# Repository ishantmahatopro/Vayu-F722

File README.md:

<h1 align="center">
  <br>
  Vayu F7
  <br>
</h1>

<h4 align="center">
A production-grade STM32F722 FPV flight controller built in KiCad, designed for
5-inch and 7-inch builds and documented the same way as a serious hardware
project should be.
</h4>

<div align="center">

</div>

<p align="center">
  <a href="#what-it-is">What it is</a> •
  <a href="#specifications">Specifications</a> •
  <a href="#hardware-overview">Hardware overview</a> •
  <a href="#pinout">Pinout</a> •
  <a href="#flight-controller-firmware">Firmware</a> •
  <a href="#building-one">Building one</a> •
  <a href="#license">License</a>
</p>

---

## What it is

*Vayu* (वायु) is the Sanskrit word for wind.

This is a 42 × 42 mm, four-layer FPV flight controller built around the
STM32F722 for 5-inch and 7-inch quads doing cinematic, telemetry, and general
performance work. It is designed to sit in the same class as well-known F722
boards while adding a cleaner power layout, a proper barometer, and a 10 V rail
sized for an HD VTX or analogue system.

The board is fully designed in KiCad.

## Specifications

| | |
|---|---|
| **MCU** | STM32F722RET6, Cortex-M7 @ 216 MHz, 512 KB flash, 256 KB RAM |
| **Gyro / accel** | ICM-42688-P on SPI1 |
| **Barometer** | BMP388 on I²C1 |
| **Blackbox** | W25Q128JVSIQ — 16 MB SPI NOR on its own bus |
| **OSD** | AT7456E analogue OSD, fitted |
| **Input** | 3S–6S (11.1–25.2 V), TVS clamp on the battery rail |
| **5 V BEC** | AP64350 synchronous buck, 5.00 V, 2 A |
| **10 V BEC** | AP64350 synchronous buck, 10.06 V, switchable for VTX rail |
| **3.3 V** | TLV62569 buck + LP5907-3.3 LDO for analogue rail |
| **Motor outputs** | 4 outputs with timer-backed DShot-capable design |
| **UARTs** | 6 total, with pads and connector-backed serial ports |
| **I²C** | 1, on the GPS connector |
| **Board** | 42 × 42 mm, 30.5 × 30.5 mm M3 mounting, 4 layers, 1.6 mm |
| **Stack-up** | F.Cu signal / **In1.Cu solid ground plane** / In2.Cu signal + ground pour / B.Cu signal |
| **Connectors** | ESC, GPS-I²C, RX, camera, VTX, USB-C |

### Power budget

| Rail | Source | Typical role |
|---|---|---|
| +10V | AP64350 buck | HD VTX / high-power video rail |
| +5V | AP64350 buck | main logic and peripheral rail |
| +3V3 | TLV62569 + LP5907 | MCU, IMU, barometer, logic |
| VBAT | input connector | raw battery feed for the switching rails |
| USB_VBUS | USB-C | debug / boot / low-power use |

## Pinout

The connector map is documented in the repo and kept together with the hardware
notes. The board includes the usual FPV stack connectors for:

| Connector | Purpose | Notes |
|---|---|---|
| ESC | Motor outputs and battery feed | 8-pin JST-SH style connector |
| GPS / I²C | GPS and barometer / compass bus | I²C and UART combination |
| HD VTX | Video and telemetry port | For HD VTX systems |
| RX | Serial receiver connection | Standard FPV receiver port |
| Camera | Camera connection | Analog / camera feed path |
| USB-C | DFU / flashing / debug | Board programming and serial access |

## Flight controller firmware

Because this project is a custom hardware layout, firmware is normally built from
upstream Betaflight or iNav sources rather than from a pre-generated target in a
factory build. The repository includes the custom target scaffold for both
firmware ecosystems so the board can be adapted to the normal upstream build
process.

### Betaflight

This repository now includes the custom Betaflight target definition at
[firmware/source/betaflight/config.h](firmware/source/betaflight/config.h).

1. Clone the upstream Betaflight repository.
2. Install the required GCC / toolchain dependencies.
3. Run `make configs` in the Betaflight tree.
4. Create a custom target directory, for example `src/config/configs/VAYUF7/`.
5. Copy [firmware/source/betaflight/config.h](firmware/source/betaflight/config.h)
   into that target directory.
6. Build the target with `make VAYUF7`.
7. Flash the resulting `.hex` via USB DFU or SWD.

The board mapping used in the target is aligned to the actual hardware:
- STM32F722RET6
- ICM-42688-P on SPI1
- BMP388 on I2C1
- AT7456E on SPI2
- W25Q128 on SPI3
- 4 motor outputs on timer-backed pins

### iNav

This repository also includes the custom iNav target files in
[firmware/source/inav/CMakeLists.txt](firmware/source/inav/CMakeLists.txt),
[firmware/source/inav/target.c](firmware/source/inav/target.c), and
[firmware/source/inav/target.h](firmware/source/inav/target.h).

1. Clone the upstream iNav repository.
2. Check out a supported stable release.
3. Create a target directory, for example `src/main/target/VAYUF7/`.
4. Copy the files from [firmware/source/inav](firmware/source/inav) into that
   target folder.
5. Configure the project with `cmake ..` inside the build directory.
6. Build the target with the normal iNav build command.
7. Flash the resulting `.hex` through USB or SWD.

> The hardware design is intentionally kept independent of any vendor-specific
> firmware stack so the board can be supported by upstream projects when the
> target is created.

## Building one

Current state — revision **R6**:

| Check | Result |
|---|---|
| KiCad DRC | **0 errors**, 0 unconnected pads (1 cosmetic silk warning) |
| KiCad ERC | **0 errors, 0 warnings** |
| Schematic ↔ board netlist | match, 483 pins / 105 nets, 0 mismatches |
| Electrical stress | all pass; worst capacitor 52.8 %, worst resistor 57.6 % of rating |
| HSE gain margin | 2.4× at C0 = 3 pF |
| Minimum via annular ring | 0.125 mm, every via ≥ 0.45 mm diameter |
| Datasheet cross-check | no mismatch found in the main design references |

The project is intentionally documented as a real engineering board, not just a
rendered concept. The repository includes a project status file, revision notes,
and hardware validation data so the design can be tracked from concept through
manufacturing readiness.

The main project constraints are documented openly:

- the board is input-limited on the battery connector at the real system level
- the 10 V rail is sized for VTX use but still obeys the regulator and layout
  limits
- all critical traces, regulator loops, and crystal areas are checked as part of
  the design review rather than left implicit

## Bill of material

The design uses practical, mainstream FPV parts that are suitable for a
production-style board and are chosen with sourcing and assembly in mind. The key
parts in the current hardware are:

| Category | Item | Notes |
|---|---|---|
| MCU | STM32F722RET6 | 32-bit F7 core, 216 MHz |
| IMU | ICM-42688-P | SPI-based gyro / accel |
| Barometer | BMP388 | I²C pressure sensor |
| Flash | W25Q128JVSIQ | 16 MB SPI NOR blackbox memory |
| OSD | AT7456E | Analog video overlay device |
| Regulators | AP64350 + LP5907 / TLV62569 | 5 V, 10 V, 3.3 V generation |
| Connectors | JST-SH / USB-C | Standard FPV and service interfaces |
| Board | 4-layer PCB | 42 × 42 mm, 30.5 × 30.5 mm mounting |

The repository is organized around the actual board design, not around a generic
marketing sheet. The hardware files, status records, and revision notes are the
source of truth for assembly and manufacturing decisions.

## BOM

The table below is the assembly BOM generated from the production files. Prices
are indicative USD unit prices from the currently displayed LCSC quantity tier
for the listed minimum order, checked on 2026-09-22. They exclude PCB
fabrication, assembly, shipping, tax, and tooling. `quote` means the public
product page did not expose a current price and should be checked in the JLCPCB
order quote.

| SL NO | LCSC NO | COMPONENT | PRICE IN USD |
|---:|---|---|---:|
| 1 | C29823 | C1, C2 - 4.7uF/50V, qty 2 | 0.0853 |
| 2 | C12891 | C10, C14, C15, C17, C8, C9 - 22uF/25V, qty 6 | 0.0904 |
| 3 | C1525 | C11, C5 - 100nF/16V, qty 2 | 0.0023 |
| 4 | C1531 | C12, C60 - 2.2nF, qty 2 | 0.0014 |
| 5 | C106203 | C13 - 22pF, qty 1 | 0.0023 |
| 6 | C3039694 | C16, C34 - 10uF/16V, qty 2 | 0.0699 |
| 7 | C307331 | C18, C21, C23, C24, C25, C26, C27, C30, C33, C35, C37, C38, C39, C40, C41, C42, C43, C46, C50, C51, C56, C58 - 100nF/50V, qty 22 | 0.0046 |
| 8 | C5199872 | C19, C20, C22, C49 - 1uF/50V, qty 4 | 0.0107 |
| 9 | C2885646 | C28, C29 - 4.7uF/16V, qty 2 | 0.0236 |
| 10 | C437557 | C3, C52, C53, C54, C55 - 4.7uF/50V, qty 5 | 0.1152 |
| 11 | C107004 | C31, C32 - 15pF, qty 2 | 0.0013 |
| 12 | C415535 | C36 - 2.2uF/16V, qty 1 | 0.0412 |
| 13 | C14663 | C4 - 100nF/50V, qty 1 | 0.0052 |
| 14 | C45783 | C47, C48 - 22uF/16V, qty 2 | 0.1037 |
| 15 | C189470 | C59 - 6.8pF, qty 1 | 0.0016 |
| 16 | C107024 | C6 - 1.8nF, qty 1 | 0.0021 |
| 17 | C107002 | C7 - 27pF, qty 1 | 0.0015 |
| 18 | C908777 | D1 - SMAJ33A, qty 1 | 0.0167 |
| 19 | C64885 | D4 - B5819W, qty 1 | 0.0091 |
| 20 | C2286 | D5 - RED 3V3, qty 1 | 0.0035 |
| 21 | C965804 | D6 - GREEN 5V, qty 1 | 0.0031 |
| 22 | C965802 | D7 - YELLOW VBAT, qty 1 | 0.0038 |
| 23 | C965807 | D8 - BLUE STATUS, qty 1 | 0.0027 |
| 24 | C1017 | FB1 - 600R@100MHz 2A, qty 1 | quote |
| 25 | C160407 | J1 - ESC 8P, qty 1 | 0.1840 |
| 26 | C53055322 | J2 - HD VTX 6P, qty 1 | 0.0349 |
| 27 | C160404 | J3 - RX 4P, qty 1 | 0.1245 |
| 28 | C53055322 | J4 - GPS/I2C 6P, qty 1 | 0.0349 |
| 29 | C160404 | J5 - CAM 4P, qty 1 | 0.1245 |
| 30 | C160404 | J6 - VTX 4P, qty 1 | 0.1245 |
| 31 | C165948 | J8 - USB-C 16P, qty 1 | 0.0971 |
| 32 | C167221 | L1 - 6.8uH FXL0630-6R8-M, qty 1 | 0.0827 |
| 33 | C189932 | L2 - 10uH SRP5030T-100M, qty 1 | 0.6640 |
| 34 | C50543 | L3 - 2.2uH SWPA4018S2R2MT, qty 1 | quote |
| 35 | C8545 | Q1 - 2N7002, qty 1 | 0.0106 |
| 36 | C20917 | Q2 - AO3400A, qty 1 | 0.0482 |
| 37 | C159047 | R1, R7 - 294k, qty 2 | 0.0004 |
| 38 | C25748 | R10 - 118k, qty 1 | 0.0013 |
| 39 | C5153958 | R11, R5 - 10.2k, qty 2 | 0.0010 |
| 40 | C2998091 | R12 - 31.6k, qty 1 | 0.0014 |
| 41 | C25744 | R13, R14, R20, R28, R34, R35, R36, R37, R38, R50 - 10k, qty 10 | 0.0017 |
| 42 | C25905 | R16, R17 - 5.1k, qty 2 | 0.0012 |
| 43 | C25879 | R18, R19, R25, R26, R39 - 2.2k, qty 5 | 0.0026 |
| 44 | C2960799 | R2, R8 - 57.6k, qty 2 | 0.0012 |
| 45 | C2909384 | R21, R22 - 75R, qty 2 | 0.0013 |
| 46 | C25804 | R23 - 10k, qty 1 | 0.0012 |
| 47 | C11702 | R24, R30, R33, R40, R41 - 1k, qty 5 | 0.0012 |
| 48 | C25741 | R27, R49 - 100k, qty 2 | 0.0013 |
| 49 | C22369194 | R29 - 100R, qty 1 | quote |
| 50 | C2909325 | R3 - 180k, qty 1 | 0.0012 |
| 51 | C25867 | R31 - 1.5k, qty 1 | 0.0013 |
| 52 | C22809 | R32 - 15k, qty 1 | 0.0014 |
| 53 | C53398 | R4 - 53.6k, qty 1 | 0.0008 |
| 54 | C2906868 | R42, R43, R44, R45, R47 - 33R, qty 5 | 0.0012 |
| 55 | C3013172 | R48 - 453k, qty 1 | 0.0013 |
| 56 | C2998160 | R6 - 25.5k, qty 1 | 0.0013 |
| 57 | C2909311 | R9 - 110k, qty 1 | 0.0009 |
| 58 | C231329 | SW1 - BOOT, qty 1 | 0.1025 |
| 59 | C2071691 | U1, U2 - AP64350SP-13, qty 2 | 1.1554 |
| 60 | C82351 | U10 - AT7456E, qty 1 | 1.7093 |
| 61 | C141836 | U3 - TLV62569DBVR, qty 1 | 0.0441 |
| 62 | C80670 | U4 - LP5907MFX-3.3, qty 1 | 0.1260 |
| 63 | C118207 | U5 - STM32F722RET6, qty 1 | 6.9322 |
| 64 | C2687116 | U6 - USBLC6-2SC6, qty 1 | 0.0221 |
| 65 | C1850418 | U7 - ICM-42688-P, qty 1 | 15.6022 |
| 66 | C779278 | U8 - BMP388, qty 1 | 3.6120 |
| 67 | C97521 | U9 - W25Q128JVSIQ, qty 1 | 1.6422 |
| 68 | C2682775 | X1 - 8MHz X32258MOB4SI 12pF, qty 1 | 0.0937 |
| 69 | C9008 | X2 - 27MHz X322527MSB4SI, qty 1 | 0.0489 |
| 70 | | PCB, qty 5 | 27.54 |
| 71 | | PCBA, qty 2 | 130

## Board renders

### - If its hard to zoom please check out /img folder to see each part of the schematic much more clearly, I tried using .pdf to .img but unfortunately u can't see the text on zooming in... hence I have taken SS of each component.

## Credits

- [KiCad](https://www.kicad.org/)
- [INAV](https://github.com/iNavFlight/inav)
- [Betaflight](https://github.com/betaflight/betaflight)
- [JLCPCB](https://jlcpcb.com/) and [LCSC](https://www.lcsc.com/)
- [Hack Club Blueprint](https://blueprint.hackclub.com/)
- The original open hardware and design process references that inspired this
  board-level documentation approach

## AI usage
This project was designed and built with the help of AI ChatGPT 5.6 precisely... AI was used to extract key important design rules for different componets pulling it off their 200pages chinglish docs ( chinese + english ). Help in creating a netlist, chosing components and drawing the schematic.
Also AI was used in writing the firmware...

> As mentioned in the resource docs, no AI was used to write slopped Journal or REAMDE.

## License

MIT

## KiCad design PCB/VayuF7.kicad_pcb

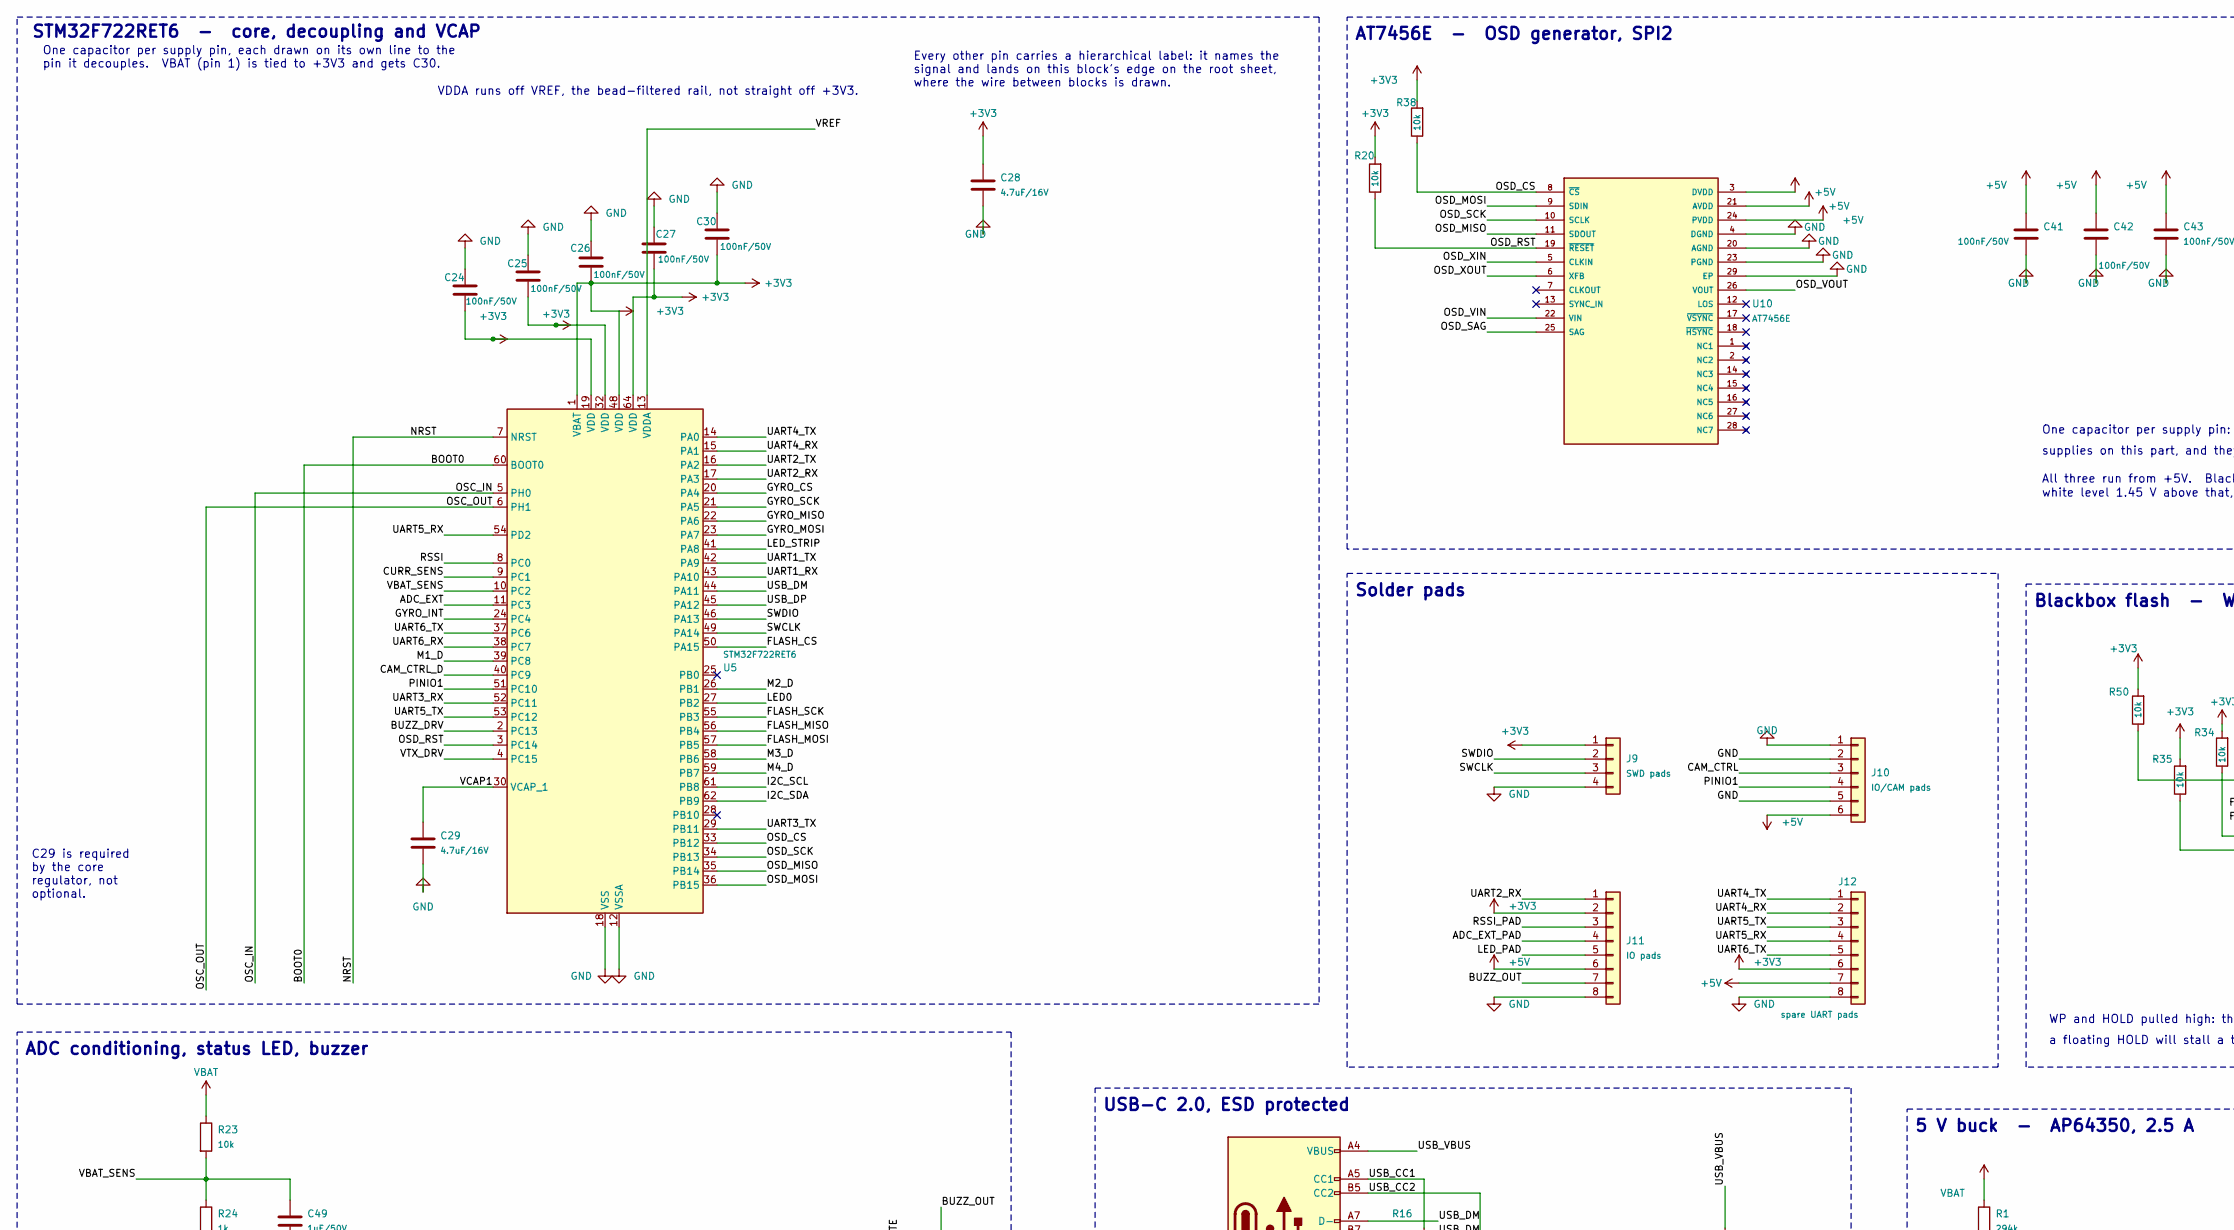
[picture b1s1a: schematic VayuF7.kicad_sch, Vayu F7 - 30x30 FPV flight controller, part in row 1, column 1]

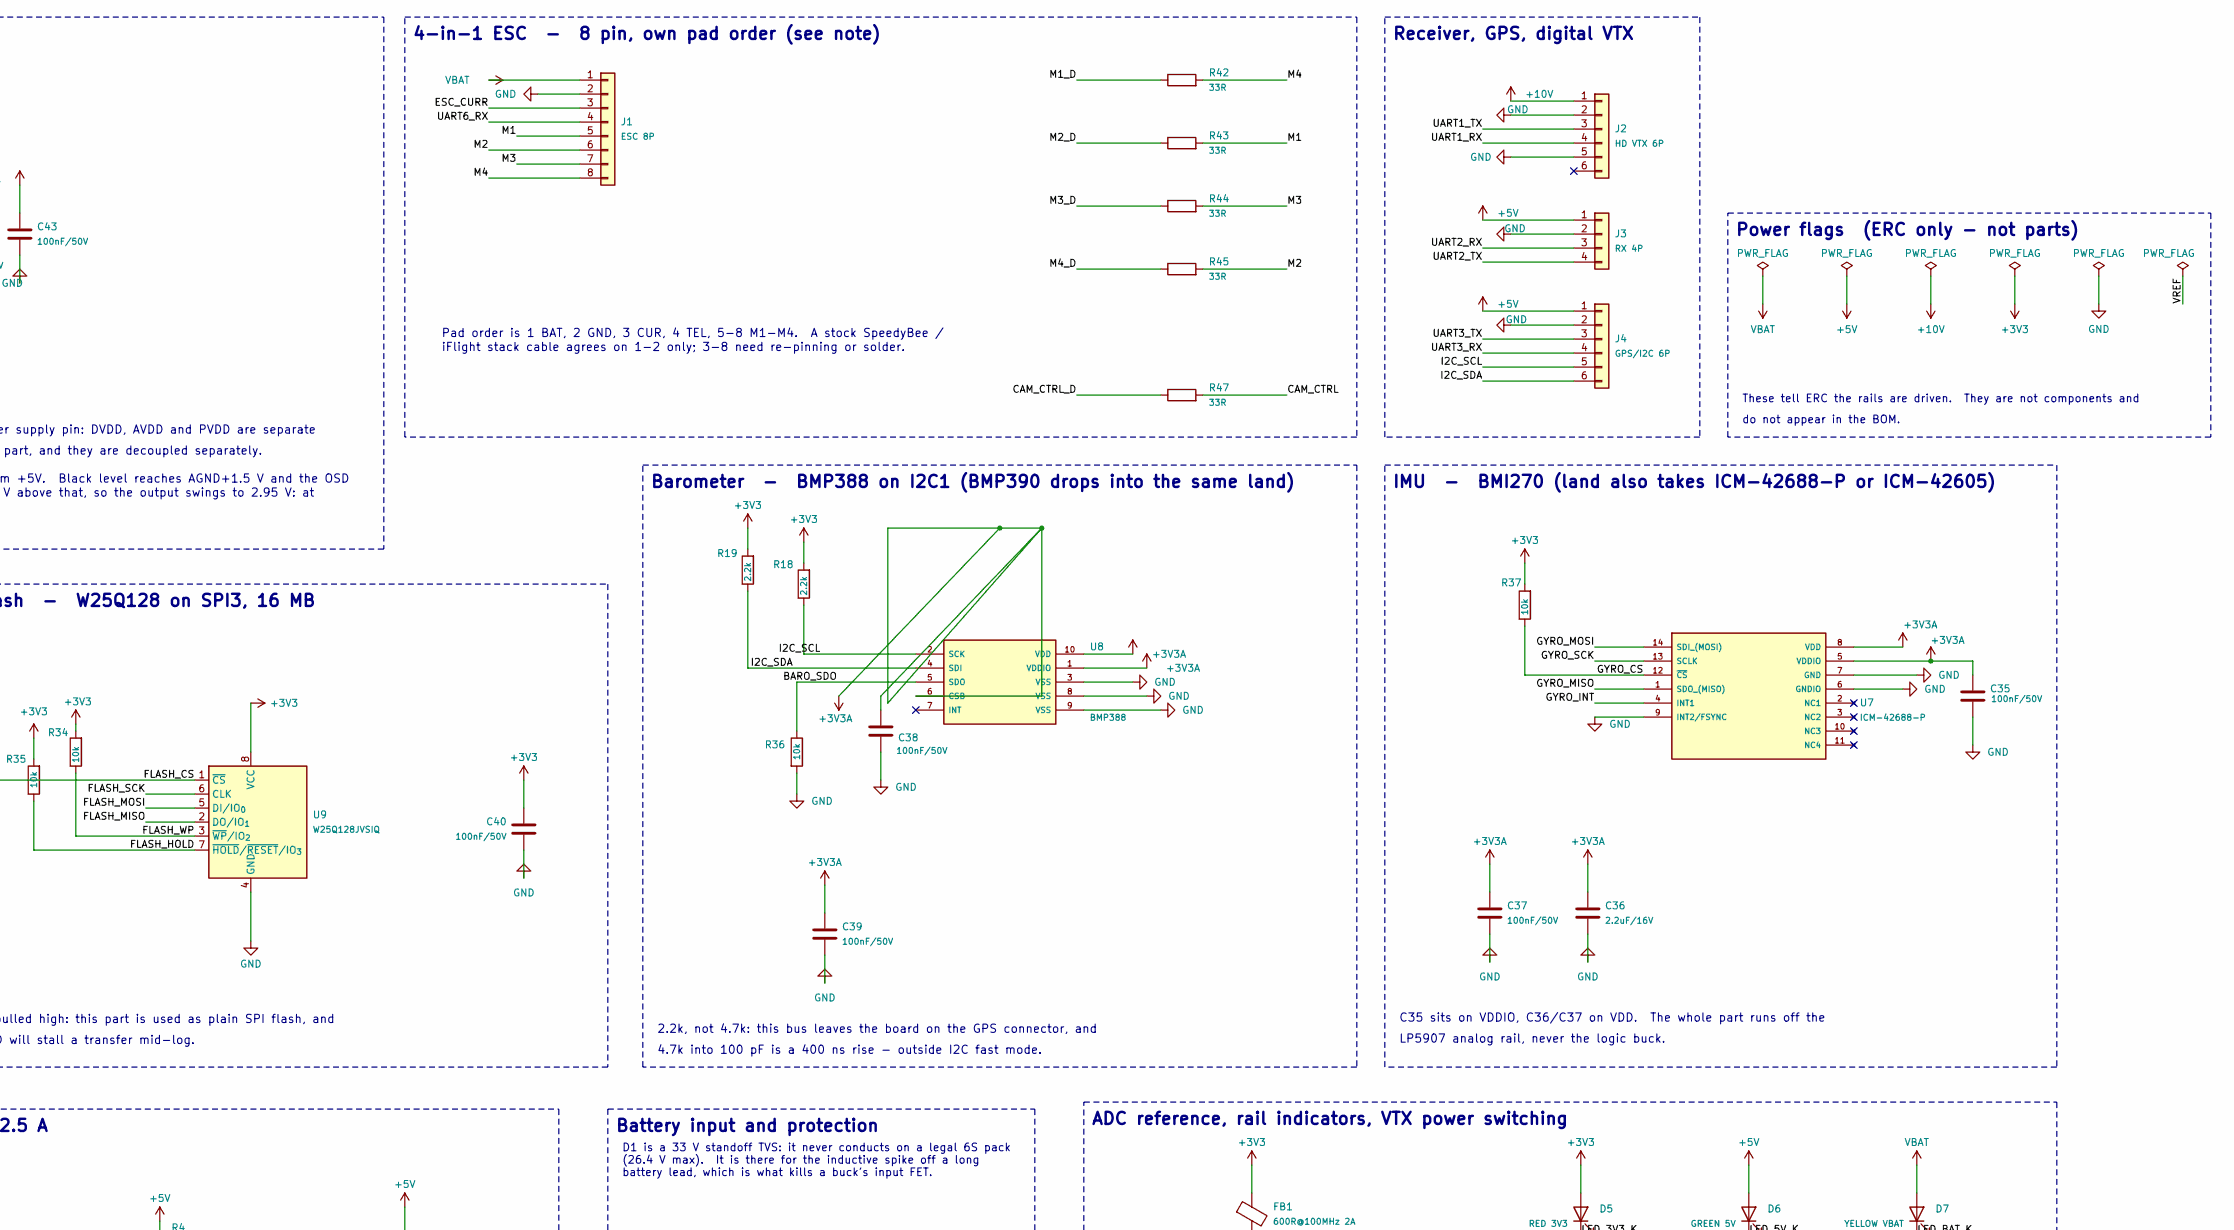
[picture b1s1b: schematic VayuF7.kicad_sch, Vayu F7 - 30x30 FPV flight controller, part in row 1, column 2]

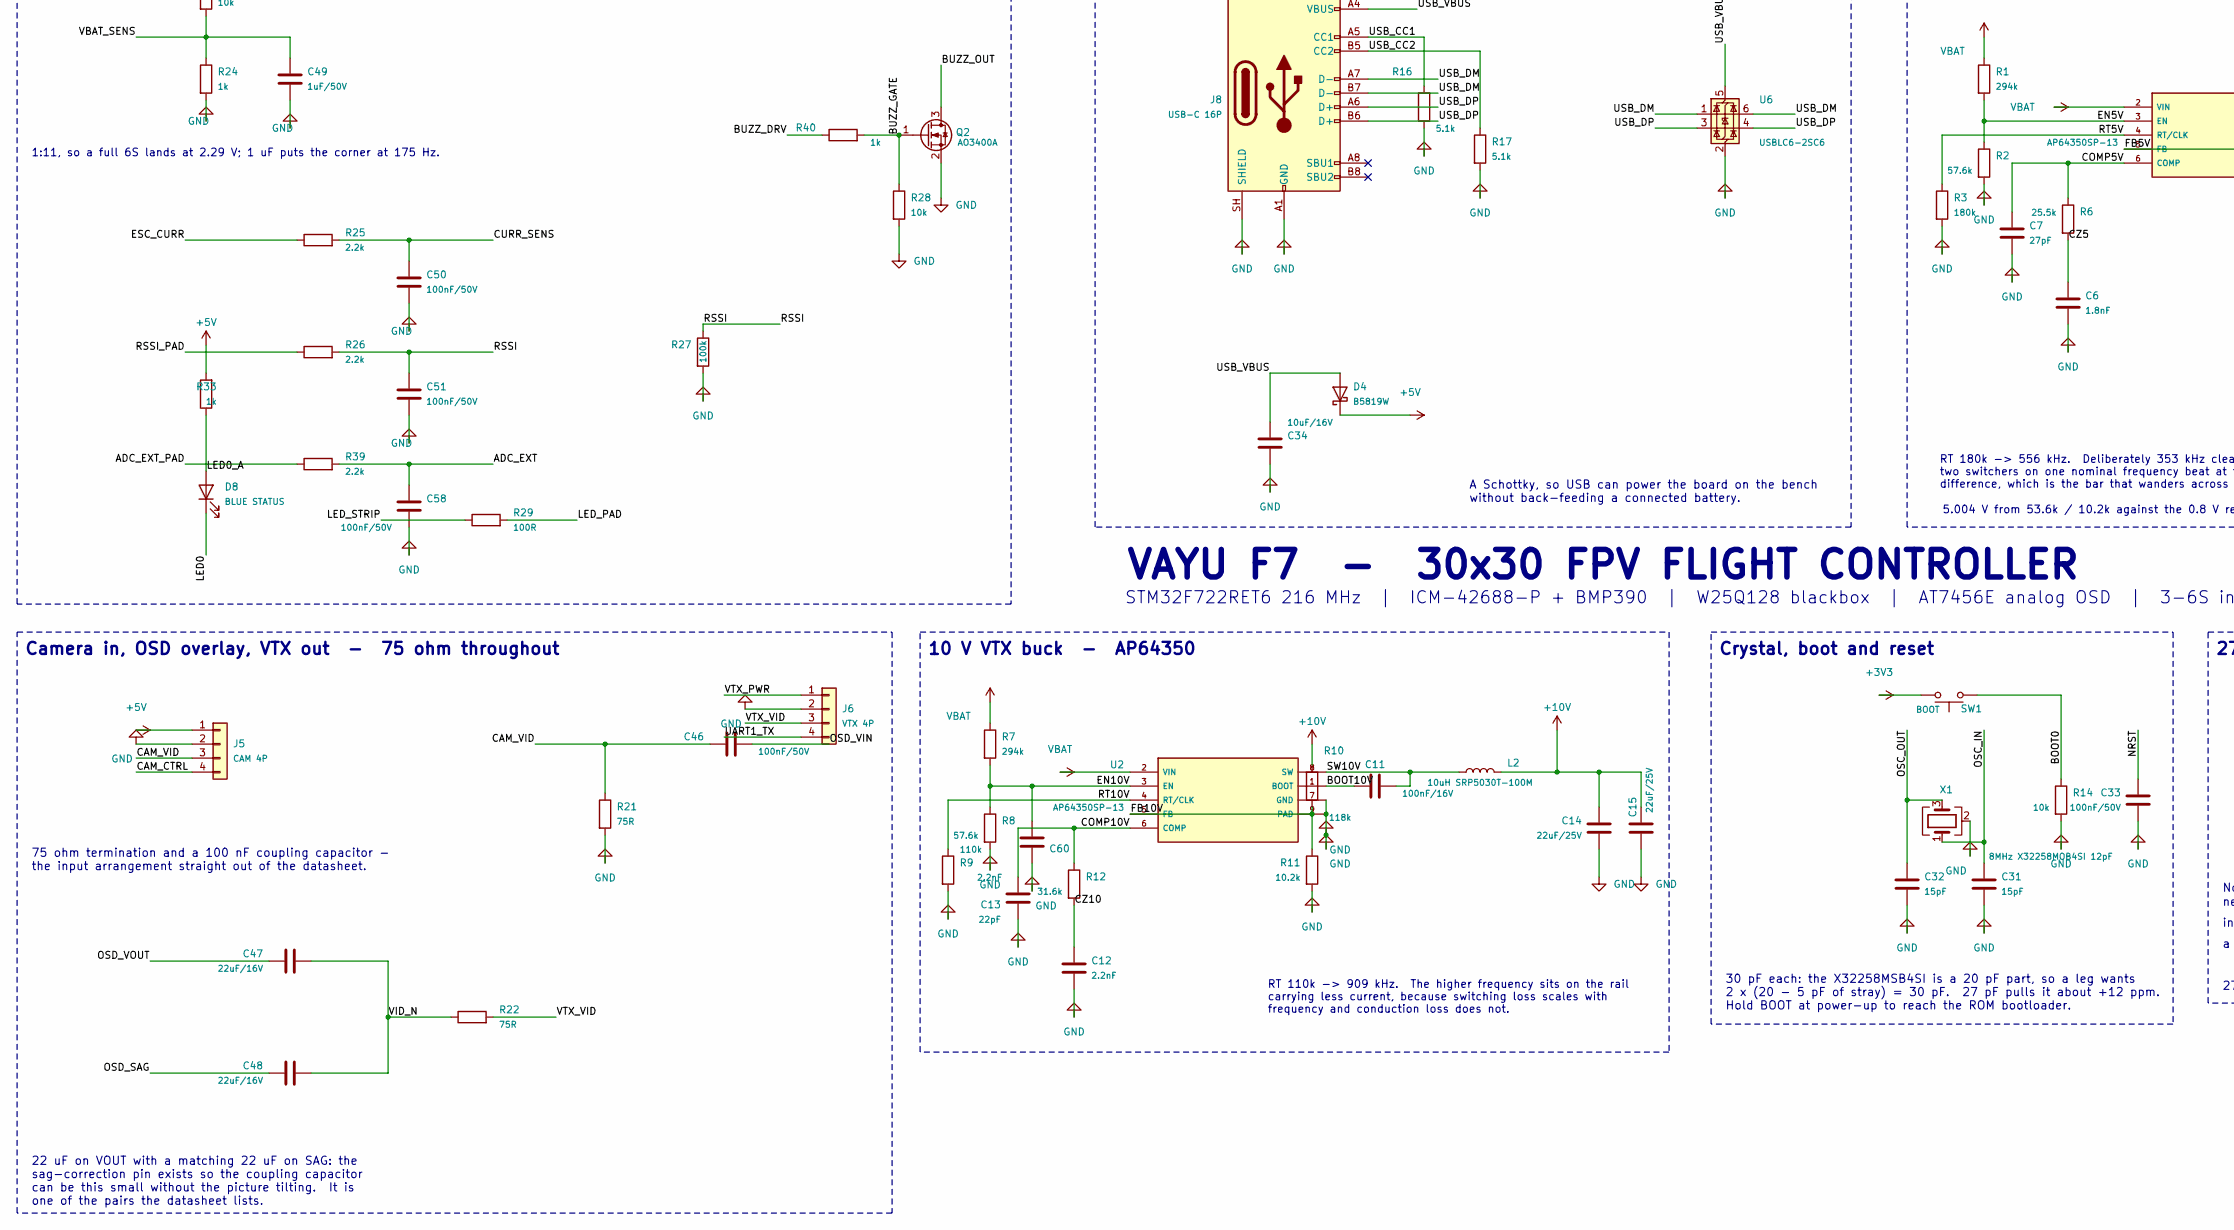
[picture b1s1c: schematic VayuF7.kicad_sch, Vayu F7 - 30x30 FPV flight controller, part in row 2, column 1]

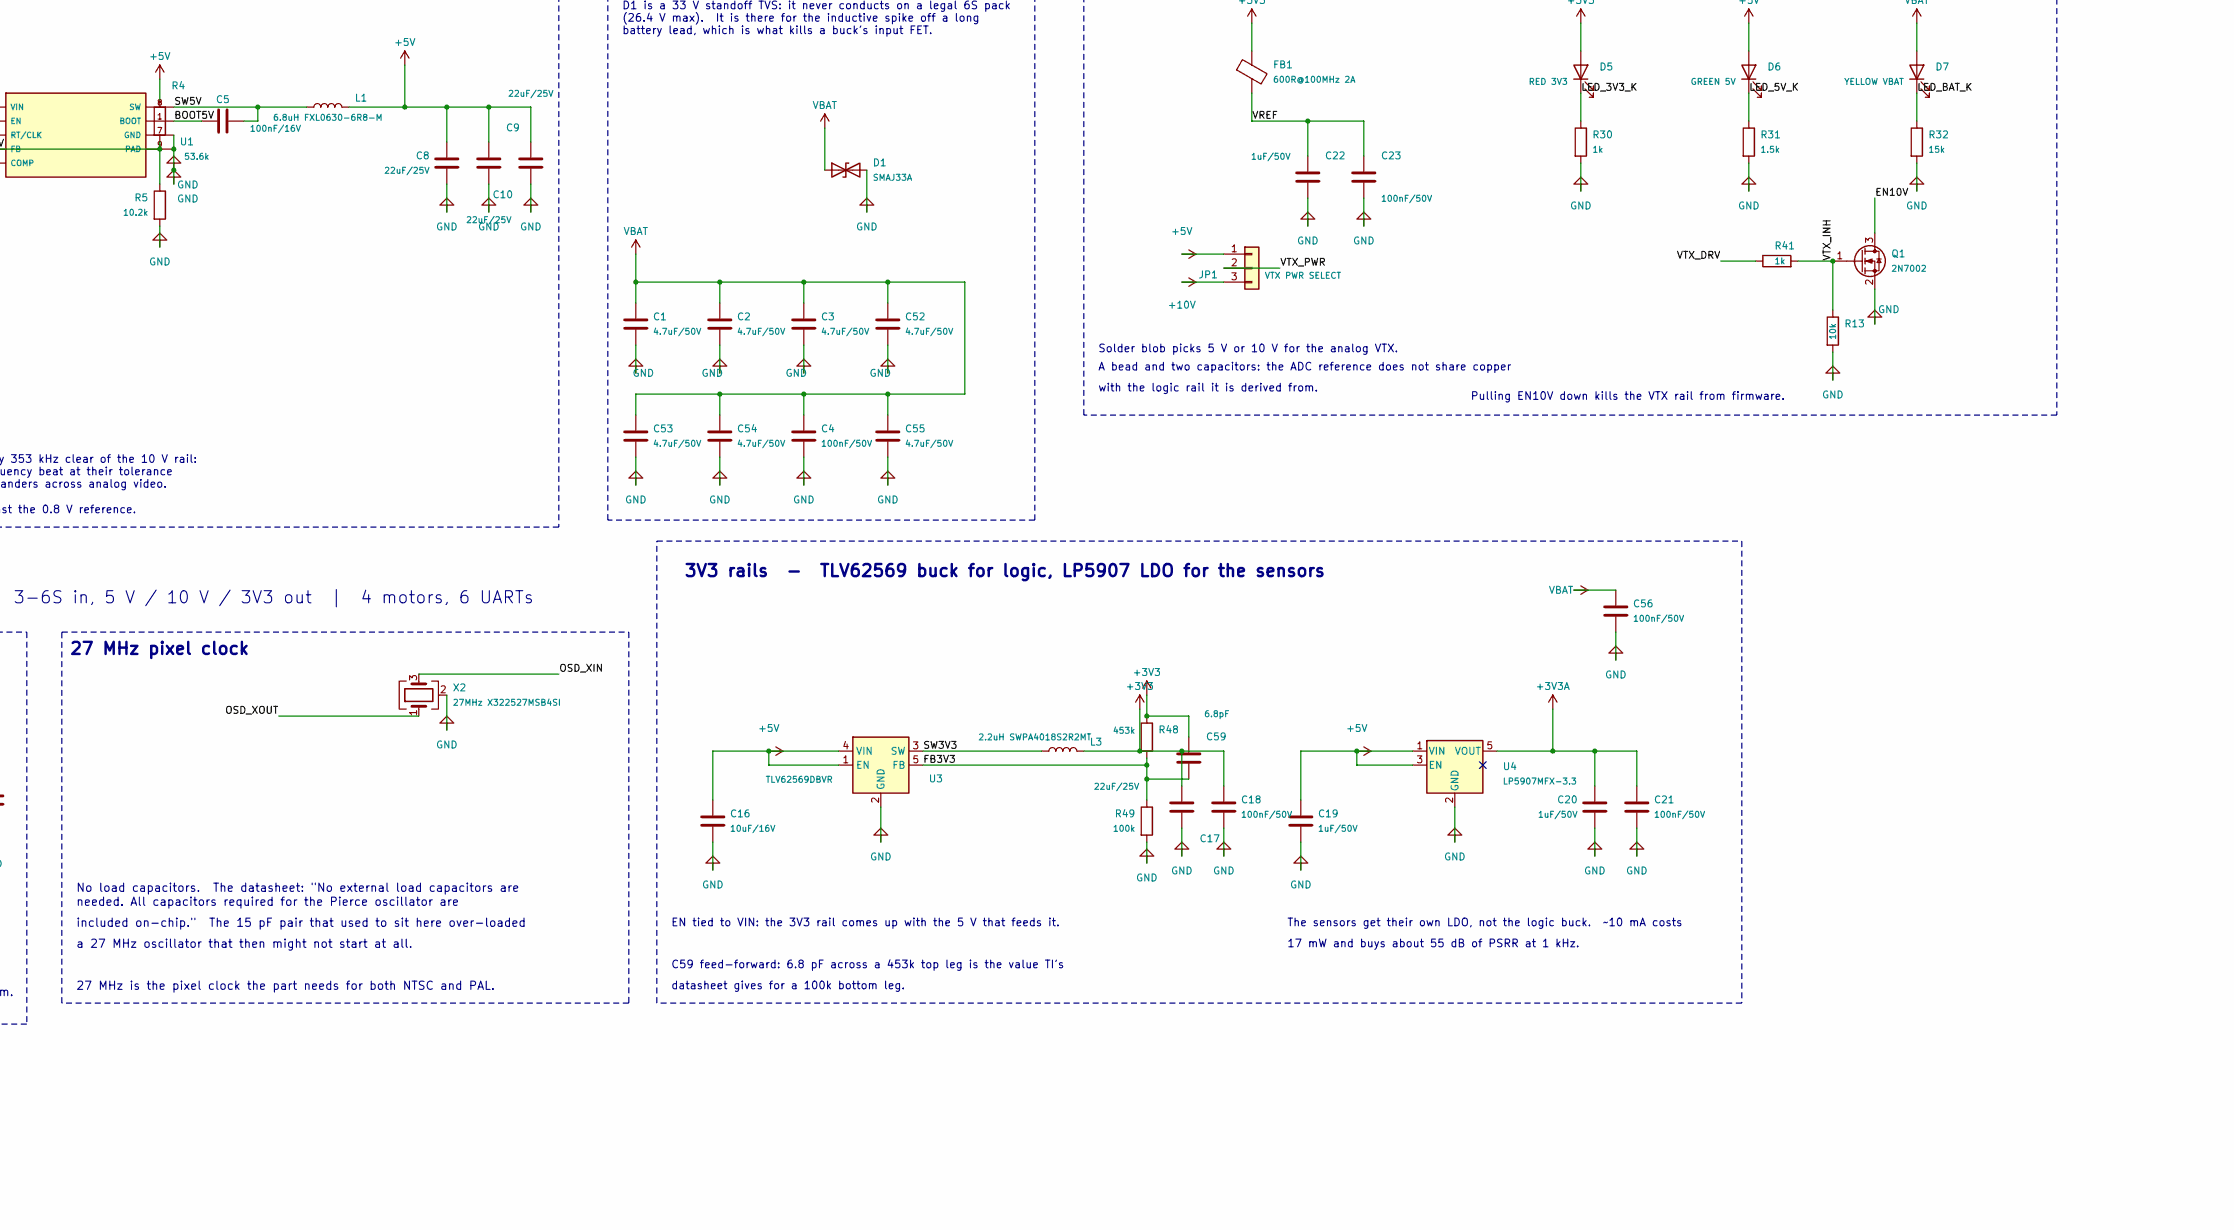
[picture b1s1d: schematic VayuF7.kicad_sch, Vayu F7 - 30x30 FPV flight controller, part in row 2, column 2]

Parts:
C1, C2: 4.7uF/50V; C_1206_3216Metric; LCSC C29823
C3, C52, C53, C54, C55: 4.7uF/50V; C_0805_2012Metric; LCSC C437557
C4: 100nF/50V; C_0603_1608Metric; LCSC C14663
C5, C11: 100nF/16V; C_0402_1005Metric; LCSC C1525
C6: 1.8nF; C_0402_1005Metric; LCSC C107024
C7: 27pF; C_0402_1005Metric; LCSC C107002
C8, C9, C10, C14, C15, C17: 22uF/25V; C_1206_3216Metric; LCSC C12891
C12, C60: 2.2nF; C_0402_1005Metric; LCSC C1531
C13: 22pF; C_0402_1005Metric; LCSC C106203
C16, C34: 10uF/16V; C_0805_2012Metric; LCSC C3039694
C18, C21, C23, C24, C25, C26, C27, C30, C33, C35, C37, C38, C39, C40, C41, C42, C43, C46, C50, C51, C56, C58: 100nF/50V; C_0402_1005Metric; LCSC C307331
C19, C20, C22, C49: 1uF/50V; C_0603_1608Metric; LCSC C5199872
C28, C29: 4.7uF/16V; C_0805_2012Metric; LCSC C2885646
C31, C32: 15pF; C_0402_1005Metric; LCSC C107004
C36: 2.2uF/16V; C_0603_1608Metric; LCSC C415535
C47, C48: 22uF/16V; C_0805_2012Metric; LCSC C45783
C59: 6.8pF; C_0402_1005Metric; LCSC C189470
D1: SMAJ33A; D_SMA; LCSC C908777
D4: B5819W; D_SOD-123; LCSC C64885
D5: RED 3V3; LED_0603_1608Metric; LCSC C2286
D6: GREEN 5V; LED_0603_1608Metric; LCSC C965804
D7: YELLOW VBAT; LED_0603_1608Metric; LCSC C965802
D8: BLUE STATUS; LED_0603_1608Metric; LCSC C965807
FB1: 600R@100MHz 2A; L_0805_2012Metric; LCSC C1017
J1: ESC 8P; JST_SH_SM08B-SRSS-TB_1x08-1MP_P1.00mm_Horizontal; LCSC C160407
J2: HD VTX 6P; JST_SH_SM06B-SRSS-TB_1x06-1MP_P1.00mm_Horizontal; LCSC C53055322
J3: RX 4P; JST_SH_SM04B-SRSS-TB_1x04-1MP_P1.00mm_Horizontal; LCSC C160404
J4: GPS/I2C 6P; JST_SH_SM06B-SRSS-TB_1x06-1MP_P1.00mm_Horizontal; LCSC C53055322
J5: CAM 4P; JST_SH_SM04B-SRSS-TB_1x04-1MP_P1.00mm_Horizontal; LCSC C160404
J6: VTX 4P; JST_SH_SM04B-SRSS-TB_1x04-1MP_P1.00mm_Horizontal; LCSC C160404
J8: USB-C 16P; USB_C_Receptacle_HRO_TYPE-C-31-M-12; LCSC C165948
J9: SWD pads; SolderPad_1x04_P1.50mm_1.0x1.6mm
J10: IO/CAM pads; SolderPad_1x06_P1.50mm_1.0x1.6mm
J11: IO pads; SolderPad_1x08_P1.50mm_1.0x1.6mm
J12: spare UART pads; SolderPad_1x08_P1.50mm_1.0x1.2mm
JP1: VTX PWR SELECT; SolderJumper-3_P1.3mm_Open_Pad1.0x1.5mm
L1: 6.8uH FXL0630-6R8-M; L_cjiang_FXL0630; LCSC C167221
L2: 10uH SRP5030T-100M; L_Bourns_SRP5030T; LCSC C189932
L3: 2.2uH SWPA4018S2R2MT; L_Sunlord_SWPA4018S; LCSC C50543
Q1: 2N7002; SOT-23; LCSC C8545
Q2: AO3400A; SOT-23; LCSC C20917
R1, R7: 294k; R_0402_1005Metric; LCSC C159047
R2, R8: 57.6k; R_0402_1005Metric; LCSC C2960799
R3: 180k; R_0402_1005Metric; LCSC C2909325
R4: 53.6k; R_0402_1005Metric; LCSC C53398
R5, R11: 10.2k; R_0402_1005Metric; LCSC C5153958
R6: 25.5k; R_0402_1005Metric; LCSC C2998160
R9: 110k; R_0402_1005Metric; LCSC C2909311
R10: 118k; R_0402_1005Metric; LCSC C25748
R12: 31.6k; R_0402_1005Metric; LCSC C2998091
R13, R14, R20, R28, R34, R35, R36, R37, R38, R50: 10k; R_0402_1005Metric; LCSC C25744
R16, R17: 5.1k; R_0402_1005Metric; LCSC C25905
R18, R19, R25, R26, R39: 2.2k; R_0402_1005Metric; LCSC C25879
R21, R22: 75R; R_0402_1005Metric; LCSC C2909384
R23: 10k; R_0603_1608Metric; LCSC C25804
R24, R30, R33, R40, R41: 1k; R_0402_1005Metric; LCSC C11702
R27, R49: 100k; R_0402_1005Metric; LCSC C25741
R29: 100R; R_0402_1005Metric; LCSC C22369194
R31: 1.5k; R_0402_1005Metric; LCSC C25867
R32: 15k; R_0603_1608Metric; LCSC C22809
R42, R43, R44, R45, R47: 33R; R_0402_1005Metric; LCSC C2906868
R48: 453k; R_0402_1005Metric; LCSC C3013172
SW1: BOOT; SW_SPST_B3U-1000P; LCSC C231329
U1, U2: AP64350SP-13; SOIC-8-1EP_3.9x4.9mm_P1.27mm_EP2.62x3.51mm; LCSC C2071691
U3: TLV62569DBVR; SOT-23-5; LCSC C141836
U4: LP5907MFX-3.3; SOT-23-5; LCSC C80670
U5: STM32F722RET6; LQFP-64_10x10mm_P0.5mm; LCSC C118207
U6: USBLC6-2SC6; SOT-23-6; LCSC C2687116
U7: ICM-42688-P; Bosch_LGA-14_3x2.5mm_P0.5mm; LCSC C1850418
U8: BMP388; Bosch_LGA-10_2x2mm_BMP388_BMP390; LCSC C779278
U9: W25Q128JVSIQ; SOIC-8_5.3x5.3mm_P1.27mm; LCSC C97521
U10: AT7456E; HTSSOP-28-1EP_4.4x9.7mm_P0.65mm_EP2.75x6.2mm; LCSC C82351
X1: 8MHz X32258MOB4SI 12pF; Crystal_SMD_3225-4Pin_3.2x2.5mm; LCSC C2682775
X2: 27MHz X322527MSB4SI; Crystal_SMD_3225-4Pin_3.2x2.5mm; LCSC C9008

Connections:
+3V3A: C20.1, C21.1, C35.1, C36.1, C37.1, C38.1, C39.1, U4.5 (VOUT), U7.5 (VDDIO), U7.8 (VDD), U8.1 (VDDIO), U8.6 (CSB), U8.10 (VDD)
ADC_EXT: C58.1, R39.2, U5.11 (PC3)
ADC_EXT_PAD: J11.4, R39.1
BARO_SDO: R36.1, U8.5 (SDO)
BOOT0: R14.1, SW1.1, U5.60 (BOOT0)
BOOT5V: C5.1, U1.1 (BOOT)
BOOT10V: C11.1, U2.1 (BOOT)
BUZZ_DRV: R40.1, U5.2 (PC13)
BUZZ_GATE: Q2.1 (G), R28.1, R40.2
BUZZ_OUT: J11.7, Q2.3 (D)
CAM_CTRL: J5.4, J10.3, R47.2
CAM_CTRL_D: R47.1, U5.40 (PC9)
CAM_VID: C46.1, J5.3, R21.1
COMP5V: C7.1, R6.1, U1.6 (COMP)
COMP10V: C13.1, R12.1, U2.6 (COMP)
CURR_SENS: C50.1, R25.2, U5.9 (PC1)
CZ5: C6.1, R6.2
CZ10: C12.1, R12.2
EN5V: R1.2, R2.1, U1.3 (EN)
EN10V: C60.1, Q1.3 (D), R7.2, R8.1, U2.3 (EN)
ESC_CURR: J1.3, R25.1
FB3V3: C59.2, R48.2, R49.1, U3.5 (FB)
FB5V: R4.2, R5.1, U1.5 (FB)
FB10V: R10.2, R11.1, U2.5 (FB)
FLASH_CS: R50.1, U5.50 (PA15), U9.1 (~CS)
FLASH_HOLD: R35.1, U9.7 (~HOLD/~RESET/IO_{3})
FLASH_MISO: U5.56 (PB4), U9.2 (DO/IO_{1})
FLASH_MOSI: U5.57 (PB5), U9.5 (DI/IO_{0})
FLASH_SCK: U5.55 (PB3), U9.6 (CLK)
FLASH_WP: R34.1, U9.3 (~WP/IO_{2})
GYRO_CS: R37.1, U5.20 (PA4), U7.12 (~CS)
GYRO_INT: U5.24 (PC4), U7.4 (INT1)
GYRO_MISO: U5.22 (PA6), U7.1 (SDO_(MISO))
GYRO_MOSI: U5.23 (PA7), U7.14 (SDI_(MOSI))
GYRO_SCK: U5.21 (PA5), U7.13 (SCLK)
I2C_SCL: J4.5, R18.1, U5.61 (PB8), U8.2 (SCK)
I2C_SDA: J4.6, R19.1, U5.62 (PB9), U8.4 (SDI)
LED0: D8.1 (K), U5.27 (PB2)
LED0_A: D8.2 (A), R33.1
LED_3V3_K: D5.1 (K), R30.1
LED_5V_K: D6.1 (K), R31.1
LED_BAT_K: D7.1 (K), R32.1
LED_PAD: J11.5, R29.2
LED_STRIP: R29.1, U5.41 (PA8)
M1: J1.5, R43.2
M1_D: R42.1, U5.39 (PC8)
M2: J1.6, R45.2
M2_D: R43.1, U5.26 (PB1)
M3: J1.7, R44.2
M3_D: R44.1, U5.58 (PB6)
M4: J1.8, R42.2
M4_D: R45.1, U5.59 (PB7)
NRST: C33.1, U5.7 (NRST)
OSC_IN: C31.1, U5.5 (PH0), X1.1
OSC_OUT: C32.1, U5.6 (PH1), X1.3
OSD_CS: R38.1, U5.33 (PB12), U10.8 (~CS)
OSD_MISO: U5.35 (PB14), U10.11 (SDOUT)
OSD_MOSI: U5.36 (PB15), U10.9 (SDIN)
OSD_RST: R20.1, U5.3 (PC14), U10.19 (~RESET)
OSD_SAG: C48.1, U10.25 (SAG)
OSD_SCK: U5.34 (PB13), U10.10 (SCLK)
OSD_VIN: C46.2, U10.22 (VIN)
OSD_VOUT: C47.1, U10.26 (VOUT)
OSD_XIN: U10.5 (CLKIN), X2.3
OSD_XOUT: U10.6 (XFB), X2.1
PINIO1: J10.4, U5.51 (PC10)
RSSI: C51.1, R26.2, R27.1, U5.8 (PC0)
RSSI_PAD: J11.3, R26.1
RT5V: R3.1, U1.4 (RT/CLK)
RT10V: R9.1, U2.4 (RT/CLK)
SW3V3: L3.1, U3.3 (SW)
SW5V: C5.2, L1.1, U1.8 (SW)
SW10V: C11.2, L2.1, U2.8 (SW)
SWCLK: J9.3, U5.49 (PA14)
SWDIO: J9.2, U5.46 (PA13)
UART1_RX: J2.4, U5.43 (PA10)
UART1_TX: J2.3, J6.4, U5.42 (PA9)
UART2_RX: J3.3, J11.1, U5.17 (PA3)
UART2_TX: J3.4, U5.16 (PA2)
UART3_RX: J4.4, U5.52 (PC11)
UART3_TX: J4.3, U5.29 (PB11)
UART4_RX: J12.2, U5.15 (PA1)
UART4_TX: J12.1, U5.14 (PA0)
UART5_RX: J12.4, U5.54 (PD2)
UART5_TX: J12.3, U5.53 (PC12)
UART6_RX: J1.4, U5.38 (PC7)
UART6_TX: J12.5, U5.37 (PC6)
USB_CC1: J8.A5 (CC1), R16.1
USB_CC2: J8.B5 (CC2), R17.1
USB_DM: J8.A7 (D-), J8.B7 (D-), U5.44 (PA11), U6.1 (I/O1), U6.6 (I/O1)
USB_DP: J8.A6 (D+), J8.B6 (D+), U5.45 (PA12), U6.3 (I/O2), U6.4 (I/O2)
USB_VBUS: C34.1, D4.2 (A), J8.A4 (VBUS), J8.A9 (VBUS), J8.B4 (VBUS), J8.B9 (VBUS), U6.5 (VBUS)
VBAT_SENS: C49.1, R23.2, R24.1, U5.10 (PC2)
VCAP1: C29.1, U5.30 (VCAP_1)
VID_N: C47.2, C48.2, R22.1
VTX_DRV: R41.1, U5.4 (PC15)
VTX_INH: Q1.1 (G), R13.1, R41.2
VTX_PWR: J6.1, JP1.2
VTX_VID: J6.3, R22.2

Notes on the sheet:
10 V VTX buck - AP64350
iFlight stack cable agrees on 1-2 only; 3-8 need re-pinning or solder.
4-in-1 ESC - 8 pin, own pad order (see note)
All three run from +5V. Black level reaches AGND+1.5 V and the OSD
One capacitor per supply pin, each drawn on its own line to the pin it decouples. VBAT (pin 1) is tied to +3V3 and gets C30.
C59 feed-forward: 6.8 pF across a 453k top leg is the value TI's
supplies on this part, and they are decoupled separately.
datasheet gives for a 100k bottom leg.
17 mW and buys about 55 dB of PSRR at 1 kHz.
a 27 MHz oscillator that then might not start at all.
EN tied to VIN: the 3V3 rail comes up with the 5 V that feeds it.
27 MHz is the pixel clock the part needs for both NTSC and PAL.
ADC conditioning, status LED, buzzer
5.004 V from 53.6k / 10.2k against the 0.8 V reference.
Crystal, boot and reset
Barometer - BMP388 on I2C1 (BMP390 drops into the same land)
C29 is required by the core regulator, not optional.
Battery input and protection
IMU - BMI270 (land also takes ICM-42688-P or ICM-42605)
Solder pads
LP5907 analog rail, never the logic buck.
with the logic rail it is derived from.
Receiver, GPS, digital VTX
Every other pin carries a hierarchical label: it names the signal and lands on this block's edge on the root sheet, where the wire between blocks is drawn.
D1 is a 33 V standoff TVS: it never conducts on a legal 6S pack (26.4 V max). It is there for the inductive spike off a long battery lead, which is what kills a buck's input FET.
RT 180k -> 556 kHz. Deliberately 353 kHz clear of the 10 V rail: two switchers on one nominal frequency beat at their tolerance difference, which is the bar that wanders across analog video.
STM32F722RET6 216 MHz | ICM-42688-P + BMP390 | W25Q128 blackbox | AT7456E analog OSD | 3-6S in, 5 V / 10 V / 3V3 out | 4 motors, 6 UARTs
1:11, so a full 6S lands at 2.29 V; 1 uF puts the corner at 175 Hz.
STM32F722RET6 - core, decoupling and VCAP
Camera in, OSD overlay, VTX out - 75 ohm throughout
22 uF on VOUT with a matching 22 uF on SAG: the sag-correction pin exists so the coupling capacitor can be this small without the picture tilting. It is one of the pairs the datasheet lists.
Pulling EN10V down kills the VTX rail from firmware.
WP and HOLD pulled high: this part is used as plain SPI flash, and
30 pF each: the X32258MSB4SI is a 20 pF part, so a leg wants 2 x (20 - 5 pF of stray) = 30 pF. 27 pF pulls it about +12 ppm. Hold BOOT at power-up to reach the ROM bootloader.
do not appear in the BOM.
white level 1.45 V above that, so the output swings to 2.95 V: at
No load capacitors. The datasheet: "No external load capacitors are
VAYU F7 - 30x30 FPV FLIGHT CONTROLLER
27 MHz pixel clock
Power flags (ERC only - not parts)

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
